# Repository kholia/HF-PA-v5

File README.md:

### HF-PA-v5

VU3CER's Robust `Class-D HF PA` for https://github.com/kholia/Easy-Digital-Beacons-v1
project for 40-20-17-15-10 bands.

For extra fun, use this PA with https://github.com/kholia/HF-Balcony-Antenna-System.

This design aspires to be the standard mW-to-QRP-Gallon HF PA in the ~600 INR
(8 USD) design space. Well, it does much more than QRP now...

Design Constraints:

- PCB is to be homebrewed.

- Only one PCB layer (side) is available for routing work.

- IRF510 MOSFET needs to be on an edge to allow usage of heatsinks.

- Typical external linears (e.g. `PA150 HF Linear Amp`) need 2W minimum to
  function. So we need a minimum of 2W of RF output from our design. Even at
  28 MHz.

- Minimal part count is strongly preferred. Low cost, and ease of availability
  are strong driving and deciding factors.

  The cost of this entire HF-PA-v5 system is less than one RD16HHF1 MOSFET ;)

- Reproducibility is a MUST! We focus a lot on this aspect by documenting each,
  and every detail possible.

- Repairability in the field is a MUST!

  Dhiru's finding: Repairing homebrewed PCBs is so much easier, and fun than
  reworking commercial `lead-free` PTH PCBs.

- No moving mechanical parts are allowed in the design - this rules out usage
  of (failure-prone) active cooling options like fans.

- We do NOT like the robustness of QCX, QDX, uSDX PAs. Removing heat from TO-92
  devices in a reliable way is not a trivial problem.

Note 0: All screenshots are clickable and zoomable.

Input: Few milliwatts is fine. Note: Si5351's output is around 8-10mW.

Output: See https://github.com/kholia/HF-PA-v4 for results.

Note 1: The output power is software controllable (via `PWM grounding`) for
flexibility.

Note 2: The idea behind making these (and my other) design notes publicly
available is to deliver REPRODUCIBLE, flexible, home-brewable, standardized,
reasonable, and cost-effective solutions for some common problems. I include
many references, simulations, and notes in my projects to enable you to do your
own (better) designs - do share them ;)

Robustness Notes:

- Ensure that the IRF510 is fastened securely to the heat sink.

  Use lock washers, and thermal epoxy adhesive to ensure good mechanical
  contact.

- We recommend operating at 24v instead of >= 29v.

Please see the older https://github.com/kholia/HF-PA-v2 project for the
power-supply (over-current protected), and LPF designs.

Schematic:

PCB rendering (v5):

Homebrew version of the same PCB:

Note 3: The HF PA is connected to a 20m dipole over 55 meters of HLF-200 coax.

Note 4: The PCB is done using [KiCad 6.x](https://www.kicad.org/download/) - a
free, and open EDA software.

Note 5: This PA can be homebrewed from scratch in around 4 to 6 hours (one
afternoon, and an evening).

#### Notes

[From QRP Labs] Si5351A outputs a 3.3v square wave. The power output of Si5351A
is around 8-10mW (10 dBm). The BS170 based driver circuit amplifies this to
~200mW (23 dBm) for a gain of around 13 dB. The IRF510 finals provide a gain of
around 14dB and produce around 5W of RF power.

Input drive matters the most in getting good RF output from IRF510. This is
precisely what Si5351A lacks (which is perfectly fine), and why the BS170
driver stage is necessary.

Important: Don't exceed the IRF510's gate limit of 1-2W. Keep the output of the
BS170 driver in check, and within the limits of IRF510.

For safety, keep the output of BS170 less than 22 or 23 Vpp by controlling the
BS170 PA voltage (via the LM317 trimpot).

#### PA tuning process

- Remove the BS170 and IRF510 MOSFETS from their sockets.

- Set DC gate bias for BS170 to 0v. Now increase the bias (via trimpot) until
  the current consumption increases slightly (QRP Labs' process).

  You can also start by setting the gate bias to 2v directly ;)

  The final bias value can be around 2.1v to 2.2v in many cases.

- For IRF510, set gate bias to 3v. This ensures that IRF510 isn't turned ON -
  double-check this by monitoring the power consumption.

- Connect the MOSFET back, and measure RF output. Happy with the output power? -
  If yes, you are done else follow the next steps.

- Remove the MOSFET, increase the gate bias voltage in very small increments
  (0.1v types).

- Connect the MOSFET back, and measure power consumption without any RF input.
  Ensure that MOSFET remains OFF without any RF input.

- Apply RF input, and measure RF output.

- Repeat these steps as needed.

The [QRP Labs' procedure for bias adjustment](https://www.qrp-labs.com/images/pa/pa_simple_assembly_A4.pdf) and [this document](https://www.qrp-labs.com/images/ultimate3s/assembly_u3s.pdf) seem to have a better description of this process.

#### PA BOM

- 1 x IRF510 (Genuine Vishay parts are tried-and-tested) - 22 to 50 INR

  - The `SEC` (`SEC Electronics Inc`) branded IRF510(s) also work great!

  - The `SEC IRF510` can perform even better than Vishay's version. This
    particular result will vary between different product batches.

  - IRF510s with `International Rectifier` branding are most likely fake or
    "new old stock" if you are very lucky!

    Note: IR and Infineon have stopped manufacturing IRF510 MOSFETs.

  - AliExpress IRF510(s) are likely to be fake

  - The IR IRF510 gave ~3W versus 5.2W+ from SEC IRF510 versus ~5W from
    Vishay's IRF510!

    Note: The gate threshold voltage can vary even between two samples picked
    from the same manufacturer!

  - The Cgs ("gate capacitance") of a fake IRF510 is typically more than 1000pF
    on a LCR-T4 meter. This value is around ~400pF for genuine IRF510 parts on
    a LCR-T4 meter.

  - Some of the fake IRF510(s) cause a short in the power supply chain
    resulting in bad things happening (TM).

    I was not aware of this problem a few years ago, and was wondering why the
    power supply fuse was blowing in a uBITX I was repairing. I didn't have the
    LCR-T4 meter back then.

  - Ensure proper sourcing (trusted supply chain, etc) to get genuine parts

- All resistors should be MFR!

- BS170 MOSFET - 9 to 15 INR

- 3 x 4.7k Preset (Potentiometer) RM-065 - 20 INR

  - It is easier to get 5k (502) trimpots

- 1 x 3.3k 0.25W MFR - 2 INR

- 1 x 4.7k 0.25W MFR - 2 INR

- 1 x 220 0.25W MFR - 2 INR

- 1 x 10 Ohm 0.25W MFR - 2 INR

- [Optional] 2 x 10k Ohm - 0.25W Metal Film Resistor - 5 INR

- A very large heat sink - 50 to 175 INR - larger heatsink is better!

- Regulator heat sink - https://etstore.in/index.php/product/aluminium-u-type-heat-sink/ - < 5 INR

- 1 x LM317 (TO-220 package) Voltage Regulator - 18 INR

- 1 x 1N4001 (or 1N4007) diode for regulator protection - 2 INR

- 2 x SMA connectors (Vertical PCB mount) - 42 INR

- 1 x 10uF 50v Electrolytic Capacitor - 3 INR

- 4 x 100nF (104) 50v MLCC - 20 INR

- 1 x 100nF (104) 100v MLCC - 20 INR

- 1 x FT37-43 (Black Toroid, Fair-Rite 5943000201) - less than 25 INR (handles <= 350mW only)

- 1 x FT50-43 (Larger Black Toroid, Fair-Rite 5943000301) - less than 32 INR

- Misc: Relimate Connectors, Glass Epoxy Copper Clad Board (PCB), Various
  Consumables (~100 INR), SMA cables for testing, RF adapter (SMA Male to
  SO-239), M3 nuts and screws, TO-220 insulator kit

- Tools: LCR-T4 Meter (for measuring things), RF Power Meter

- Optional power supply: LM50-20B24 Mornsun SMPS - 24V 2.2A - 52.8W AC/DC SMPS - 700 INR

- Optional PPTC fuse

- PA Total Cost: Less than 600 INR

#### Power Supply + LPF BOM

See the following projects:

- https://github.com/kholia/HF-PA-v2
- https://github.com/kholia/HF-PA-v3
- https://github.com/kholia/HF-PA-v4
- 2 x 100 pF (50/100v)
- 1 x 180 pF (50/100v)
- 2 x T50-6 (Yellow Iron Dust code) toroids
- 25 SWG Winding Wire

Note: For LPF, use C0G 100v rated caps!

#### BOM + Equipment Sources

- https://www.semikart.com/ (IRF510, BS170, 100v NP0 LPF caps - Kemet and others)

  - 100v NP0 LPF caps from `Multicomp Pro` brand seem pretty cost-effective

  - 1N5374B 75V 5W Zener Diode (optional - for SWR protection)

  - https://www.semikart.com/search/5943000301 (FT50-43 toroid)

  - https://www.semikart.com/search/5943000201 (FT37-43 toroid)

- https://www.dnatechindia.com/ (Vishay IRF510) - send them an email to confirm
  the brand you are going to get!

- https://rarecomponents.com (BS170)

- https://www.electronicscomp.com/

  - Regular caps, ST voltage regulators

  - Female berg strip (2.54mm pitch)

  - PCB Etching Powder - FECL3 - Ferric-Ferrous Chloride

- https://www.electroncomponents.com/ (transistors, connectors, consumables, misc)

  - https://www.electroncomponents.com/BS170-N-channel-Switching-FET

  - https://www.electroncomponents.com/LM317-Adjustable-Regulator

  - https://www.electroncomponents.com/1N4001

  - https://www.electroncomponents.com/mica-insulator-to-220-set-kit

- https://www.sunrom.com/ (regular ceramic caps, SMA connectors)

- https://projectpoint.in/

  - Transistors, regular caps, voltage regulators, pots / trimmers, MFR resistors, misc

  - 2-Pin High Quality Relimate Connectors (all those 2-pin headers are actually Relimate Connectors)

  - Copper Magnetic Winding Wire - 29 SWG and 25 SWG

  - LM317 voltage regulator

  - 3-Pin Relimate Cable Female to Female (High Quality 2500mA) - 'TO-220 socket'

  - 2-Pin Relimate Cable Female (High Quality 2500mA) - for power

  - 2-Pin Relimate Male Header

- Semikart, eBay (`gr_makis`) - Toroids

- https://www.onlinetps.com/shop/ ('IR branded' IRF510 - not recommended at all - avoid!)

- https://www.electronicscomp.com/ (they ship 'IR branded' IRF510s at times, so avoid)

- https://www.ktron.in/

  - https://www.ktron.in/product/lm317-regulator-ic-to-220/

  - https://www.ktron.in/product/sma-connector-straight/

- [LCR-T4 LCR Meter](https://www.techtonics.in/lcr-t4-12864-lcd-graphical-transistor-tester-resistance-capacitance-esr-scr-meter)

- https://robu.in/ (voltage boost module)

- https://www.ktron.in/product/40x1-round-header-female-2mm-pitch/

  Sunrom also has these.

- TO-92 heatsink - DIY or get `AAVID THERMALLOY 575200B00000G TO-92 Package` heatsink

- Household items

  - Hot iron ("press")

  - Laser printer - I use the `toner transfer using hot iron` method for making PCBs at home

- See https://github.com/kholia/HF-PA-v2 and https://github.com/kholia/HF-PA-v3 sources too

Note for international buyers: The BOM can be carefully sourced via Mouser and DigiKey.

#### O(Current consumption)

The ESP8266 usually draws a peak current of about 250mA after it wakes up and
then more or less constantly draws around 70mA before it goes back to sleep.

DS3231 -> 5mA

Si5351 -> ~50 to 100mA

PA -> Less than 1 A (rms)

Upper bound -> 1.4A maximum.

#### Tips

MOSFETs are sensitive with regards to ESD and high soldering temperatures. Use
best practices when dealing with MOSFETs and perhaps always ;)

By using these `TO-220 Sockets`, we can easily support any MOSFET pinout. This
technique allows usage of `off-pcb` heat sinks with a lot of flexibility. It
also avoids common ESD + MOSFET problems as well. The gate bias can be easily
checked by safely removing the MOSFET from the TO-220 socket. Also, this socket
idea allows us to safely eliminate the LDO from the design.

Note: Keep the length of the `TO-220 Sockets` as short as possible.

Also, use a `SIP socket` (aka 40×1 Round Header Female Berg Strip) for the
BS170 MOSFET.

A burnt 78(L)05 regulator can easily eat up 4-5W of power by itself. If there
is no RF output but power is being consumed then check your linear regulator.

#### Mods

If you have 1-to-2 W of RF input drive available, then remove the BS170 driver
stage altogether. The rest of the circuit works as it is.

#### Future ideas

- Use a `PPTC fuse` in the PA voltage line (oscillations are a real problem,
  and can be nasty) - Sandeep Lohia (VU3SXT).

  [Alternate] For testing purposes, I am using a current-limited power supply.

- Add a `Type K Thermocouple` based temperature monitoring to ensure safety.

- Alternatively, use ACS712 to monitor the current consumption to ensure
  safety.

- Better still, use a power supply (module) with constant current limiting.

- Add foldback current limiting - see `QRP Labs` docs.

- Add negative feedback - see `QRP Labs 10W HF Linear Power Amplifier` design.

#### References

See [References.md](./References.md).

#### Credits

This design uses ideas, and support from Hans Summers (G0UPL, QRP Labs), VU3SXT
(Sandeep Lohia), VU2ASH, Mr. Bhatnagar (VU2SPF), AC7LX, and PY2OHH.

Also see https://github.com/kholia/HF-PA-v3#credits and https://github.com/kholia/HF-PA-v2#credits.

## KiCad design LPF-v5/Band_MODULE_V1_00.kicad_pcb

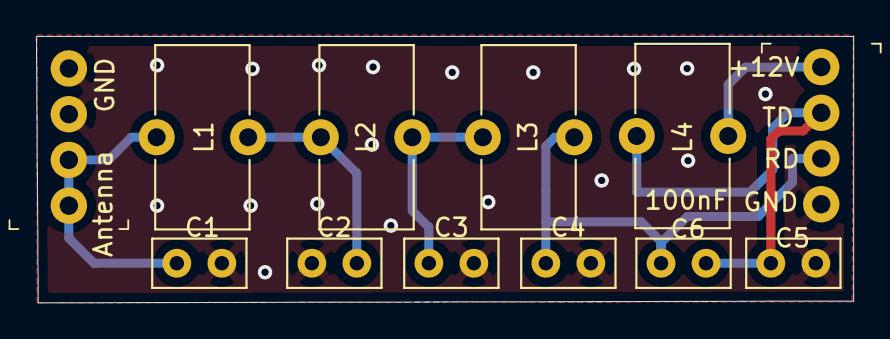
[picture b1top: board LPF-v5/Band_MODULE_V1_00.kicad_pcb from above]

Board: 2 copper layers, 45.4 x 14.8 mm, 12 parts (0 on the bottom side), 7 nets.

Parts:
C1, C2, C3, C4, C5: C_Disc_D5.0mm_W2.5mm_P2.50mm
C6: 100nF; C_Disc_D5.0mm_W2.5mm_P2.50mm
J1: Antenna; PinHeader_1x4_P2.54mm_Drill1.02mm
J2: input; PinHeader_1x4_P2.54mm_Drill1.02mm
L1, L2, L3: L_Toroid_Vertical_L10.0mm_W5.0mm_P5.08mm
L4: T37_2; L_Toroid_Vertical_L10.0mm_W5.0mm_P5.08mm

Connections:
GNDPWR: C1.2, C2.2, C3.2, C4.2, C5.1, J1.3, J1.4, J2.4
unnamed: C1.1, J1.1, J1.2, L1.1
unnamed: C2.1, L1.2, L2.1
unnamed: C3.1, L2.2, L3.1
unnamed: C4.1, C6.2, J2.3, L3.2
unnamed: C5.2, C6.1, J2.2, L4.2
unnamed: J2.1, L4.1

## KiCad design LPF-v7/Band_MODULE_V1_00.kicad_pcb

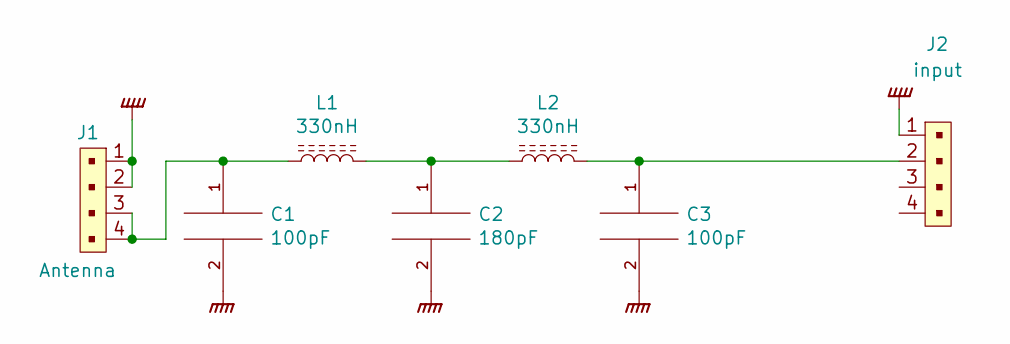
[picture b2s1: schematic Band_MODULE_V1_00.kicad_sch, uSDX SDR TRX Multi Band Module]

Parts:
C1, C3: 100pF; C_Disc_D5.0mm_W2.5mm_P2.50mm
C2: 180pF; C_Disc_D5.0mm_W2.5mm_P2.50mm
J1: Antenna; PinHeader_1x4_P2.54mm_Drill1.02mm; MPN 0022232041; Digi-Key_PN WM4202-ND
J2: input; PinHeader_1x4_P2.54mm_Drill1.02mm; MPN 0022232041; Digi-Key_PN WM4202-ND
L1, L2: 330nH; L_Toroid_Vertical_L10.0mm_W5.0mm_P5.08mm

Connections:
GNDPWR: C1.2, C2.2, C3.2, J1.1, J1.2, J2.1
unnamed: C1.1, J1.3, J1.4, L1.1
unnamed: C2.1, L1.2, L2.1
unnamed: C3.1, J2.2, L2.2

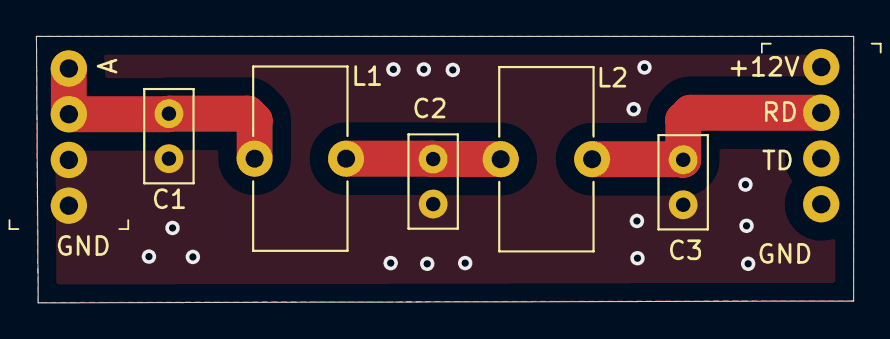
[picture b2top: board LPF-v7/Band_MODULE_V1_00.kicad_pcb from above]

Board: 2 copper layers, 45.4 x 14.8 mm, 7 parts (0 on the bottom side), 4 nets.

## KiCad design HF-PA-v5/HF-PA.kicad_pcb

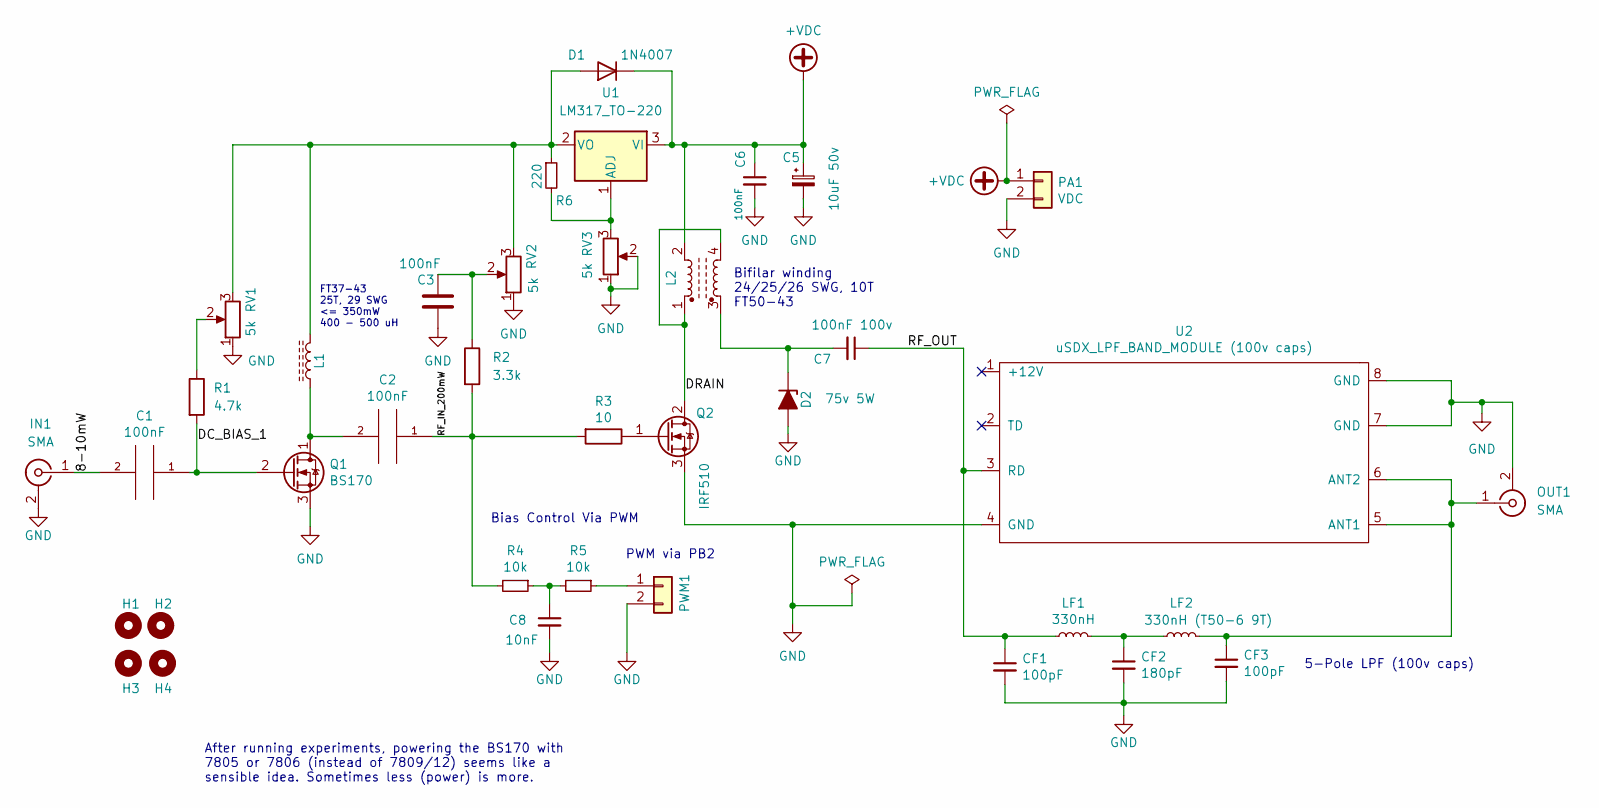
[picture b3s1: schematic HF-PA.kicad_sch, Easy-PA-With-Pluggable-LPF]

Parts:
C1, C2, C3, C6: 100nF; C_Disc_D4.3mm_W1.9mm_P5.00mm
C5: 10uF 50v; CP_Radial_D5.0mm_P2.50mm
C7: 100nF 100v; C_Disc_D4.3mm_W1.9mm_P5.00mm
C8: 10nF; C_Disc_D4.3mm_W1.9mm_P5.00mm
CF1, CF3: 100pF; C_Disc_D4.3mm_W1.9mm_P5.00mm
CF2: 180pF; C_Disc_D4.3mm_W1.9mm_P5.00mm
D1: 1N4007; D_DO-41_SOD81_P2.54mm_Vertical_KathodeUp
D2: 75v 5W; D_DO-201_P5.08mm_Vertical_AnodeUp
H1, H2, H3, H4: MountingHole; MountingHole_2.2mm_M2
IN1: SMA; SMA_Amphenol_901-144_Vertical
L1: L_Ferrite; L_Toroid_Vertical_L10.0mm_W5.0mm_P5.08mm
L2: L_Ferrite_Coupled; FT50-43 Transformer
LF1: 330nH; FT50-43 INDUCTOR
LF2: 330nH (T50-6 9T); FT50-43 INDUCTOR
OUT1: SMA; SMA_Amphenol_901-144_Vertical
PA1: VDC; PinHeader_1x02_P2.54mm_Vertical
PWM1: Conn_01x02; PinHeader_1x02_P2.54mm_Vertical
Q1: BS170; PinSocket_1x03_P2.54mm_Vertical
Q2: IRF510; TO-220-3_Vertical
R1: 4.7k; R_Axial_DIN0207_L6.3mm_D2.5mm_P2.54mm_Vertical
R2: 3.3k; R_Axial_DIN0207_L6.3mm_D2.5mm_P2.54mm_Vertical
R3: 10; R_Axial_DIN0204_L3.6mm_D1.6mm_P5.08mm_Horizontal
R4, R5: 10k; R_Axial_DIN0207_L6.3mm_D2.5mm_P2.54mm_Vertical
R6: 220; R_Axial_DIN0207_L6.3mm_D2.5mm_P2.54mm_Vertical
RV1, RV2, RV3: 5k; Potentiometer_Runtron_RM-065_Vertical
U1: LM317_TO-220; TO-220-3_Vertical
U2: uSDX_LPF_BAND_MODULE (100v caps); uSDX_LPF_Band_Module

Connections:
+VDC: C5.1, C6.1, D1.1 (K), L2.2, PA1.1, U1.3 (VI)
/8-10mW: C1.2, IN1.1 (In)
/DC_BIAS_1: C1.1, Q1.2 (G), R1.2
/DRAIN: L2.1, L2.4, Q2.2 (D)
/RF_IN_200mW: C2.1, R2.2, R3.2, R4.2
/RF_OUT: C7.1, CF1.1, LF1.1, U2.3 (RD)
GND: C3.2, C5.2, C6.2, C8.2, CF1.2, CF2.2, CF3.2, D2.2 (A), IN1.2 (Ext), OUT1.2 (Ext), PA1.2, PWM1.2, Q1.3 (S), Q2.3 (S), RV1.1, RV2.1, RV3.1, RV3.2, U2.4 (GND), U2.7 (GND), U2.8 (GND)
unnamed: C2.2, L1.1, Q1.1 (D)
unnamed: C3.1, R2.1, RV2.2
unnamed: C7.2, D2.1 (K), L2.3
unnamed: C8.1, R4.1, R5.2
unnamed: CF2.1, LF1.2, LF2.1
unnamed: CF3.1, LF2.2, OUT1.1 (In), U2.5 (ANT1), U2.6 (ANT2)
unnamed: D1.2 (A), L1.2, R6.1, RV1.3, RV2.3, U1.2 (VO)
unnamed: PWM1.1, R5.1
unnamed: Q2.1 (G), R3.1
unnamed: R1.1, RV1.2
unnamed: R6.2, RV3.3, U1.1 (ADJ)

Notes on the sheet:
After running experiments, powering the BS170 with 7805 or 7806 (instead of 7809/12) seems like a sensible idea. Sometimes less (power) is more.
Bifilar winding 24/25/26 SWG, 10T FT50-43
FT37-43 25T, 29 SWG <= 350mW 400 - 500 uH
5-Pole LPF (100v caps)
Bias Control Via PWM
PWM via PB2

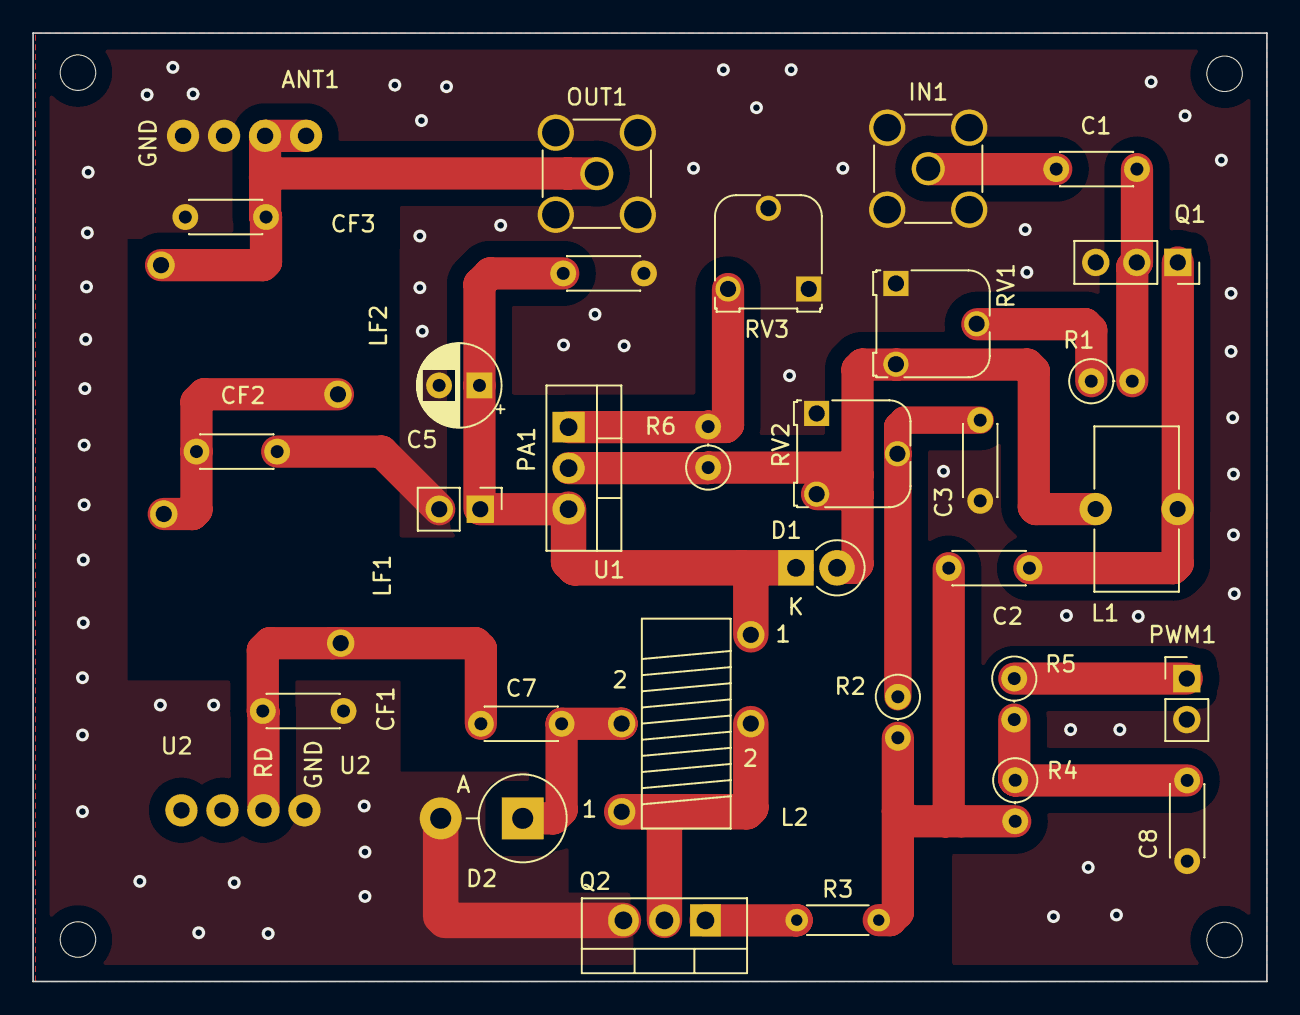
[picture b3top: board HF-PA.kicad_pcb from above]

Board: 2 copper layers, 76.4 x 58.8 mm, 37 parts (0 on the bottom side), 18 nets.

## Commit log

2022-05-03 Initial PoC
